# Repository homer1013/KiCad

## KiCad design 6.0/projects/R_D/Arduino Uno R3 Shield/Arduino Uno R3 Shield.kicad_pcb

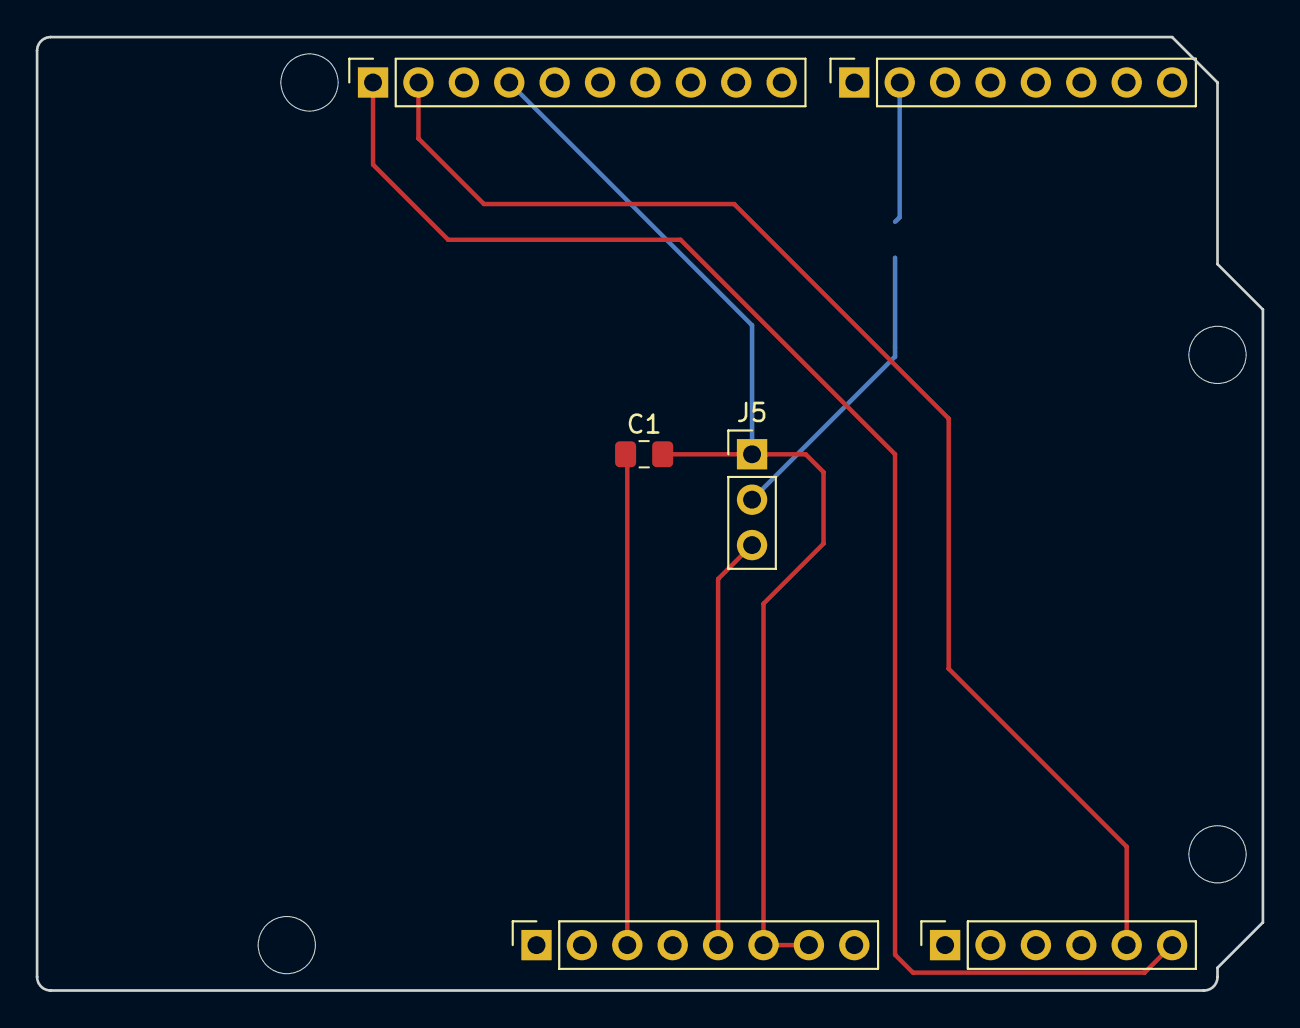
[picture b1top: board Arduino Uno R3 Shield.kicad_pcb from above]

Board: 2 copper layers, 68.6 x 53.3 mm, 11 parts (1 on the bottom side), 7 nets.

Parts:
C1: 10uF; C_0805_2012Metric_Pad1.18x1.45mm_HandSolder
J1: Power; PinSocket_1x08_P2.54mm_Vertical
J2: Digital/PWM; PinSocket_1x10_P2.54mm_Vertical
J3: Analog; PinSocket_1x06_P2.54mm_Vertical
J4: Digital/PWM; PinSocket_1x08_P2.54mm_Vertical
J5: UPDI; PinHeader_1x03_P2.54mm_Vertical
MH1, MH2, MH3, MH4: MountingHole_3.2mm
R1: 4.7ohm; R_0805_2012Metric_Pad1.20x1.40mm_HandSolder

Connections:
+5V: J1.5, J5.3
/*6: J4.2, R1.2
/SCL/A5: J2.1, J3.6
/SDA/A4: J2.2, J3.5
/~RESET: C1.1, J1.3
GND: C1.2, J1.6, J1.7, J2.4, J5.1
unnamed: J5.2, R1.1

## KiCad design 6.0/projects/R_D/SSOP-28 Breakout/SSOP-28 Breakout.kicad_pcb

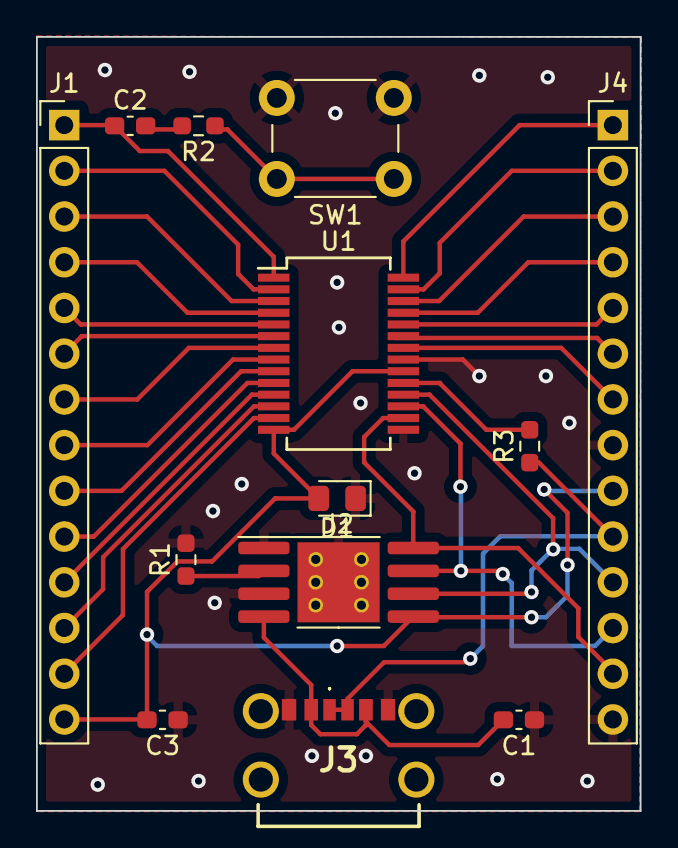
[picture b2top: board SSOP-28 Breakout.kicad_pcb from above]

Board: 2 copper layers, 33.5 x 43.0 mm, 13 parts (0 on the bottom side), 31 nets.

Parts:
C1, C2, C3: 10uF; C_0603_1608Metric_Pad1.08x0.95mm_HandSolder
D1: D_Schottky; D_0805_2012Metric_Pad1.15x1.40mm_HandSolder
J1, J4: Conn_01x14; PinHeader_1x14_P2.54mm_Vertical
J2: TP4056; SOP-8-1EP_4.57x4.57mm_P1.27mm_EP4.57x4.45mm_ThermalVias
J3: USB4125-GF-A-0190; USB4125GFA0190
R1: 2.5K; R_0603_1608Metric_Pad0.98x0.95mm_HandSolder
R2: 1K; R_0603_1608Metric_Pad0.98x0.95mm_HandSolder
R3: 4.7K; R_0603_1608Metric_Pad0.98x0.95mm_HandSolder
SW1: SW_Push_Dual; SW_PUSH_6mm_H5mm
U1: ATMEGA3208-XFR; SSOP-28_5.3x10.2mm_P0.65mm

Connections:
GND: C1.1, C3.1, D1.1 (K), J2.1 (TEMP1), J2.3 (GND_3), J2.9 (EP), J3.A12 (GND_1), J3.B12 (GND_2), J4.8, J4.14, R1.2, SW1.2, U1.15 (GND_1), U1.21 (GND_2)
unnamed: C1.2, J2.4 (VCC4), J3.A9 (VBUS_1), J3.B9 (VBUS_2)
unnamed: C2.1, J1.1, U1.1 (PA7)
unnamed: C2.2, R2.2
unnamed: C3.2, D1.2 (A), J1.14, J2.5 (BAT), J4.9, U1.14 (AVDD), U1.20 (VDD)
unnamed: J1.2, U1.2 (PC0)
unnamed: J1.3, U1.3 (PC1)
unnamed: J1.4, U1.4 (PC2)
unnamed: J1.5, U1.5 (PC3)
unnamed: J1.6, U1.6 (PD0)
unnamed: J1.7, U1.7 (PD1)
unnamed: J1.8, U1.8 (PD2)
unnamed: J1.9, U1.9 (PD3)
unnamed: J1.10, U1.10 (PD4)
unnamed: J1.11, U1.11 (PD5)
unnamed: J1.12, U1.12 (PD6)
unnamed: J1.13, U1.13 (PD7)
unnamed: J2.2 (PROG2), R1.1
unnamed: J2.6 (~STDBY), J4.11, U1.18 (PF6)
unnamed: J2.7 (~CHRG), J4.12, U1.17 (PF1(TOSC2))
unnamed: J2.8 (CE), J4.13, U1.16 (PF0(TOSC1))
unnamed: J3.A5 (CC1), J3.B5 (CC2), J4.10, R3.1
unnamed: J4.1, U1.28 (PA6)
unnamed: J4.2, U1.27 (PA5)
unnamed: J4.3, U1.26 (PA4)
unnamed: J4.4, U1.25 (PA3)
unnamed: J4.5, U1.24 (PA2)
unnamed: J4.6, U1.23 (PA1)
unnamed: J4.7, U1.22 (PA0(EXTCLK))
unnamed: R2.1, SW1.1
unnamed: R3.2, U1.19 (UPDI)

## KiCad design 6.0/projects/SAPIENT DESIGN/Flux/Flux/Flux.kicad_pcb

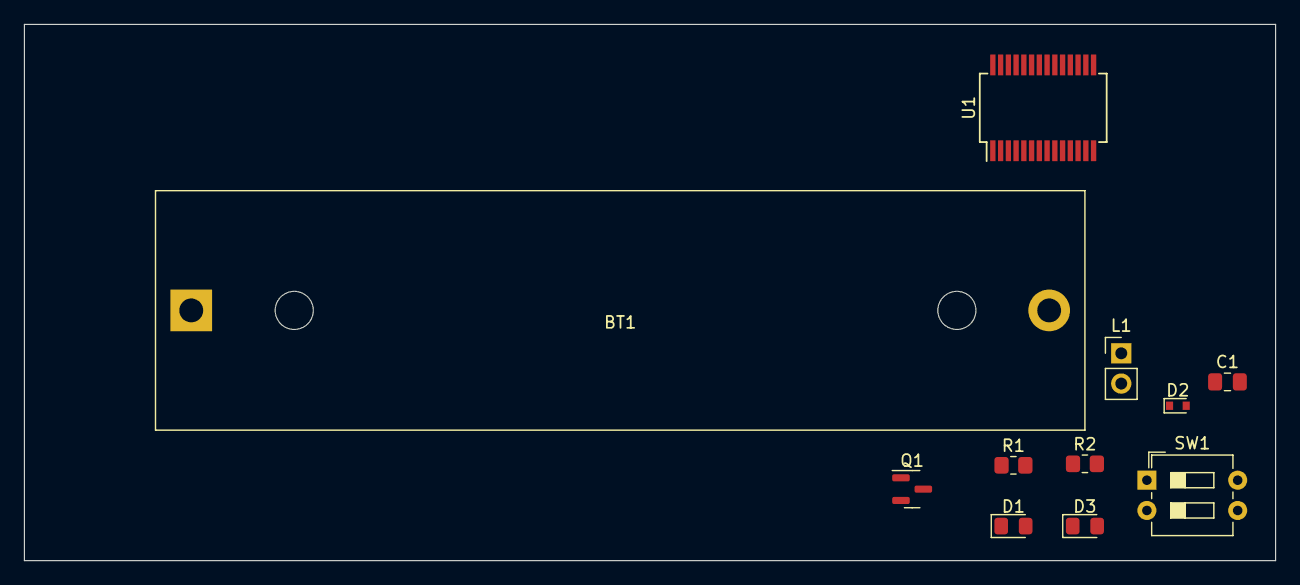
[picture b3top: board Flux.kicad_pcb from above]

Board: 2 copper layers, 105.0 x 45.0 mm, 11 parts (0 on the bottom side), 9 nets, no tracks yet.

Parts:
BT1: Battery_Cell; BatteryHolder_MPD_BH-18650-PC2
C1: C; C_0805_2012Metric_Pad1.18x1.45mm_HandSolder
D1, D3: LED; LED_0805_2012Metric_Pad1.15x1.40mm_HandSolder
D2: 1N914WT; D_SOD-523
L1: L; PinHeader_1x02_P2.54mm_Vertical
Q1: AO3400A; SOT-23
R1, R2: R; R_0805_2012Metric_Pad1.20x1.40mm_HandSolder
SW1: SW_SPDT; SW_DIP_SPSTx02_Slide_6.7x6.64mm_W7.62mm_P2.54mm_LowProfile
U1: ATmega3208-X; SSOP-28_5.3x10.2mm_P0.65mm

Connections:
GND: BT1.2 (-), D1.1 (K), D3.1 (K), Q1.2 (S), U1.15 (GND), U1.21 (GND)
unnamed: BT1.1 (+), C1.1, D2.2 (A)
unnamed: C1.2, L1.2
unnamed: D1.2 (A), R1.1
unnamed: D2.1 (K), SW1.2 (B)
unnamed: D3.2 (A), R2.1
unnamed: L1.1, Q1.3 (D)
unnamed: Q1.1 (G), R1.2, U1.6 (PD0)
unnamed: R2.2, SW1.1 (A), U1.14 (AVDD), U1.20 (VDD)

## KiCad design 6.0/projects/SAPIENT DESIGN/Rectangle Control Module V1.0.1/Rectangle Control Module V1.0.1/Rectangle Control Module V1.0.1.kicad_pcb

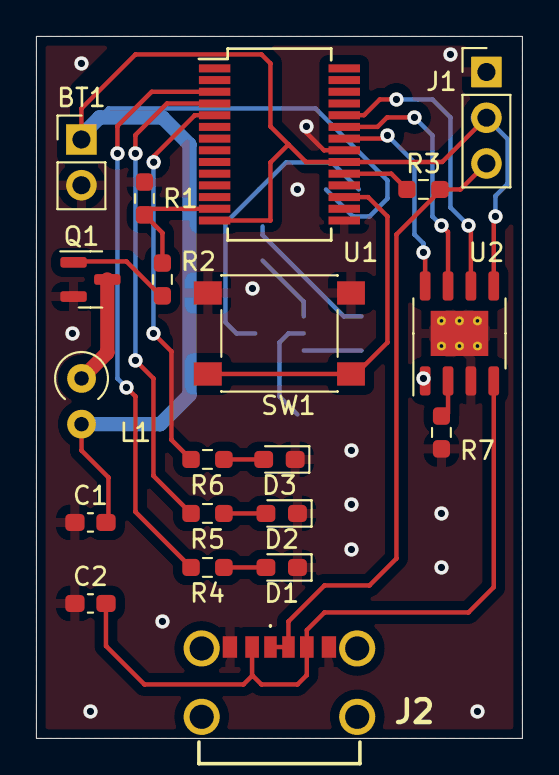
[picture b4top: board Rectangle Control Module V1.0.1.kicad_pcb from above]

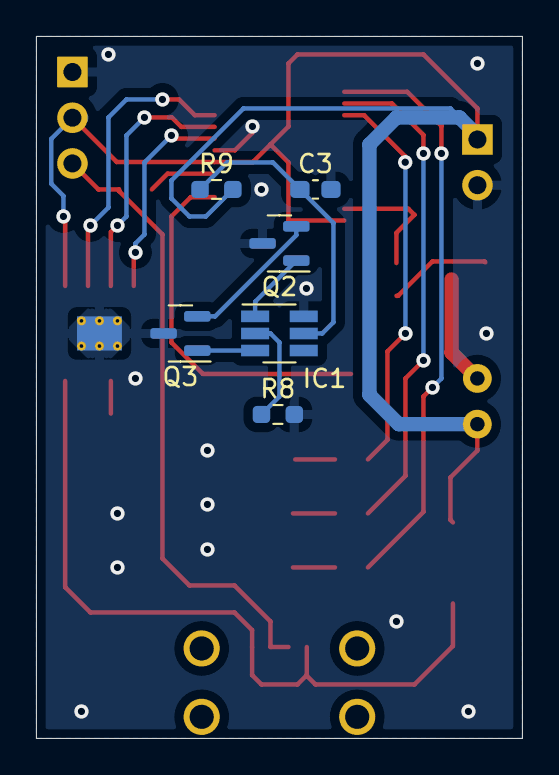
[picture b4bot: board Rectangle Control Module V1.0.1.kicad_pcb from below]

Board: 2 copper layers, 27.0 x 39.0 mm, 26 parts (6 on the bottom side), 24 nets.

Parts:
BT1: Battery_Cell; PinHeader_1x02_P2.54mm_Vertical
C1, C2: 10uF; C_0603_1608Metric_Pad1.08x0.95mm_HandSolder
C3: .1uF; C_0603_1608Metric_Pad1.08x0.95mm_HandSolder
D1, D2, D3: LED; LED_0603_1608Metric_Pad1.05x0.95mm_HandSolder
IC1: DW01A-G; SOT-23-6_Handsoldering
J1: Conn_01x03_Male; PinHeader_1x03_P2.54mm_Vertical
J2: USB4140-GF-0070-C; USB4125GFA0190
L1: 2 Ohm; L_Axial_L6.6mm_D2.7mm_P2.54mm_Vertical_Vishay_IM-2
Q1, Q2, Q3: AO3400A; SOT-23
R1: 100K; R_0603_1608Metric_Pad0.98x0.95mm_HandSolder
R2, R3: 4.7K; R_0603_1608Metric_Pad0.98x0.95mm_HandSolder
R4, R5, R6: 1K; R_0603_1608Metric_Pad0.98x0.95mm_HandSolder
R7: 2.8K; R_0603_1608Metric_Pad0.98x0.95mm_HandSolder
R8: 2K; R_0603_1608Metric_Pad0.98x0.95mm_HandSolder
R9: 330; R_0603_1608Metric_Pad0.98x0.95mm_HandSolder
SW1: btn; SW_Push_1P1T_NO_6x6mm_H9.5mm
U1: ATmega3208-X; SSOP-28_5.3x10.2mm_P0.65mm
U2: TP4056; SOIC-8-1EP_3.9x4.9mm_P1.27mm_EP2.514x3.2mm_ThermalVias

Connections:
GND: BT1.2 (-), C1.1, C2.1, C3.2, D1.1 (K), D2.1 (K), D3.1 (K), IC1.6 (GND), J1.1, J2.A12 (GND_1), J2.B12 (GND_2), Q1.2, Q2.3, Q3.3, R1.1, R7.2, R8.2, SW1.1, U1.15 (GND), U1.21 (GND), U2.1 (TEMP1), U2.3 (GND_3), U2.9 (EP)
unnamed: BT1.1 (+), C1.2, J1.2, L1.2, R9.2, U1.14 (AVDD), U1.20 (VDD), U2.5 (BAT)
unnamed: C2.2, J2.A9 (VBUS_1), J2.B9 (VBUS_2), U2.4 (VCC4)
unnamed: C3.1, IC1.5 (VCC), R9.1
unnamed: D1.2 (A), R4.1
unnamed: D2.2 (A), R5.1
unnamed: D3.2 (A), R6.1
unnamed: IC1.1 (OD), Q2.1
unnamed: IC1.2 (CS), R8.1
unnamed: IC1.3 (OC), Q3.1
unnamed: J1.3, J2.A5 (CC1), J2.B5 (CC2), R3.2
unnamed: L1.1, Q1.3
unnamed: Q1.1, R2.1
unnamed: Q2.2, Q3.2
unnamed: R1.2, R2.2, U1.13 (PD7)
unnamed: R3.1, U1.19 (UPDI)
unnamed: R4.2, U1.3 (PC1)
unnamed: R5.2, U1.4 (PC2)
unnamed: R6.2, U1.5 (PC3)
unnamed: R7.1, U2.2 (PROG2)
unnamed: SW1.2, U1.17 (PF1/TOSC2)
unnamed: U1.22 (EXTCLK/PA0), U2.8 (CE)
unnamed: U1.23 (PA1), U2.7 (~CHRG)
unnamed: U1.24 (PA2), U2.6 (~STDBY)

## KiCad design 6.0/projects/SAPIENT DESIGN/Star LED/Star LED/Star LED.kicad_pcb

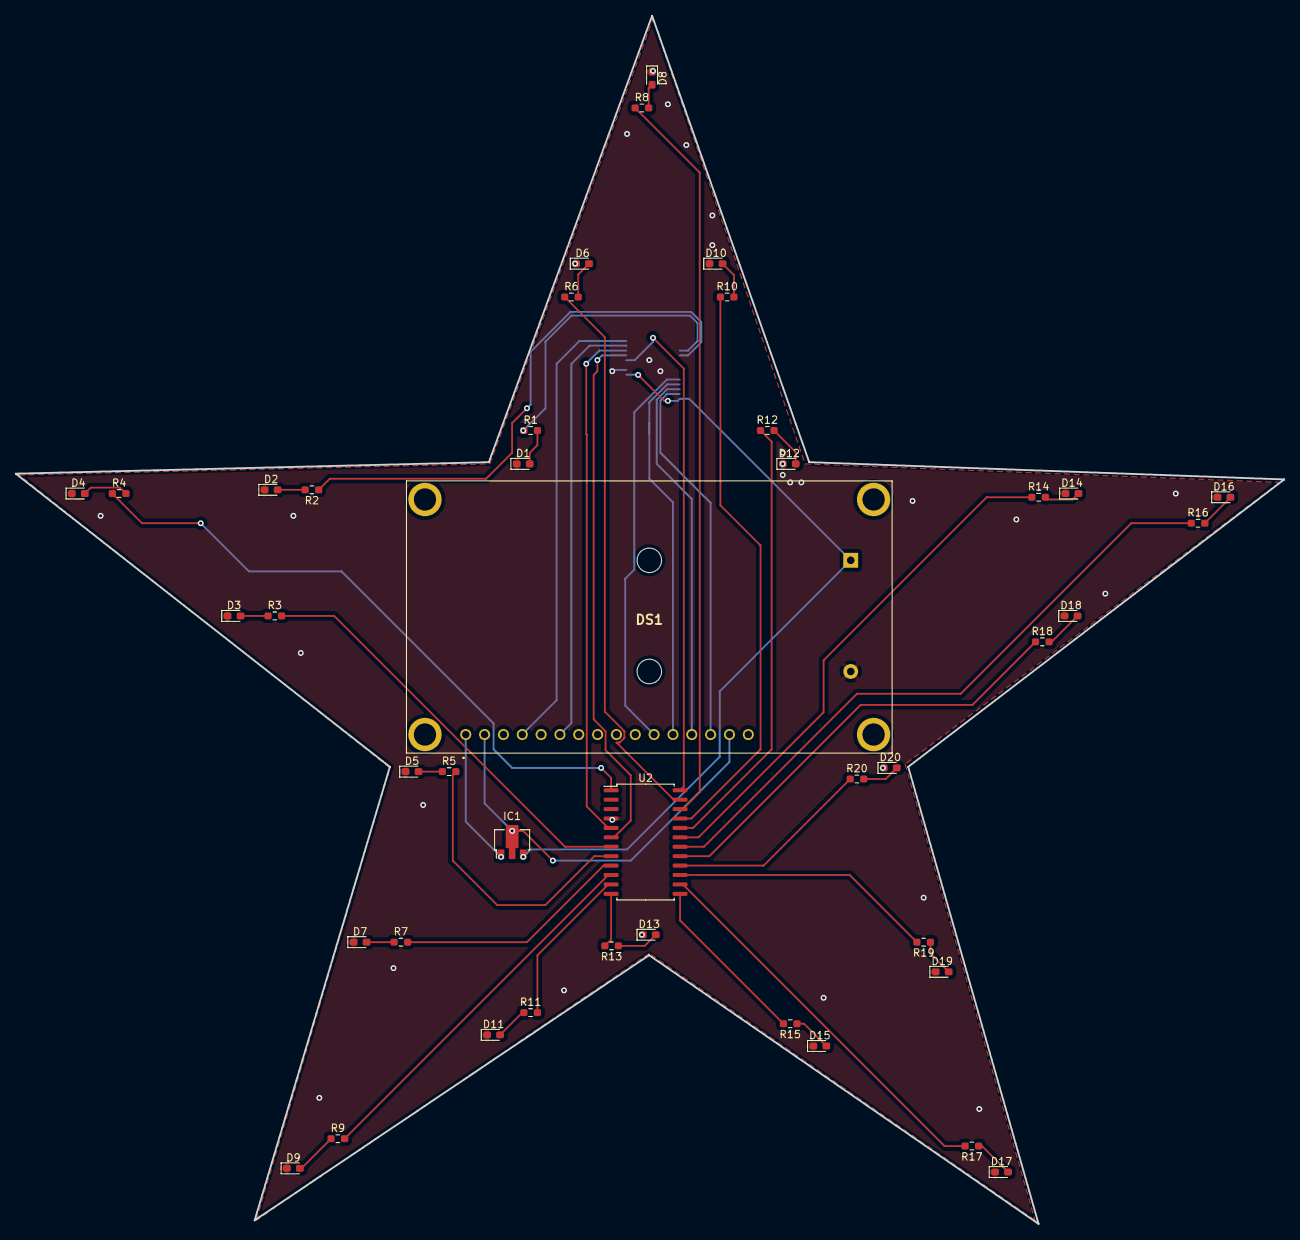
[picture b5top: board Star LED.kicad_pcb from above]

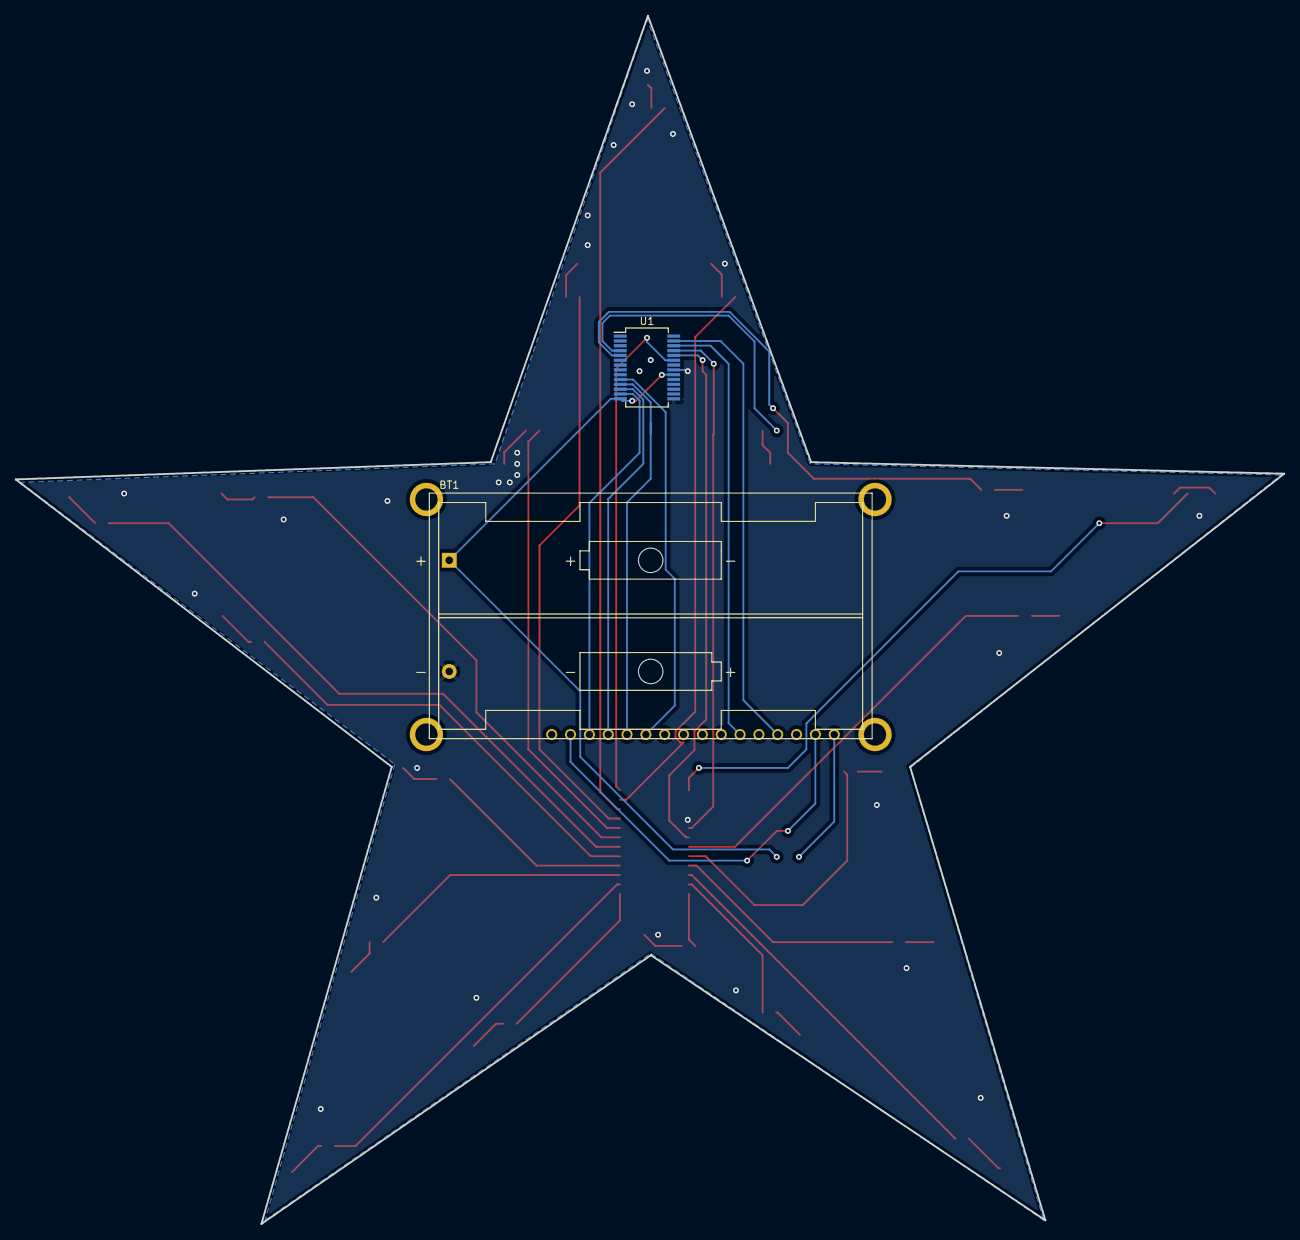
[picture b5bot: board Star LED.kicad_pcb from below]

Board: 2 copper layers, 171.1 x 162.9 mm, 45 parts (2 on the bottom side), 53 nets.

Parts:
BT1: Battery; BatteryHolder_Keystone_2462_2xAA
D1, D2, D3, D4, D5, D6, D7, D8, D9, D10, D11, D12, D13, D14, D15, D16, D17, D18, D19, D20: LED; LED_0603_1608Metric_Pad1.05x0.95mm_HandSolder
DS1: NHD-0216HZ-FSW-FBW-33V3C; NHD0216HZFSWFBW33V3C
IC1: MCP1702T-3302E_CB; SOT-89-3
R1, R2, R3, R4, R5, R6, R7, R8, R9, R10, R11, R12, R13, R14, R15, R16, R17, R18, R19, R20: R; R_0603_1608Metric_Pad0.98x0.95mm_HandSolder
U1: ATmega3208-X; SSOP-28_5.3x10.2mm_P0.65mm
U2: IS31FL3218-GR; SOP-24_7.5x15.4mm_P1.27mm

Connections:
GND: BT1.2 (-), D1.1 (K), D2.1 (K), D3.1 (K), D4.1 (K), D5.1 (K), D6.1 (K), D7.1 (K), D8.1 (K), D9.1 (K), D10.1 (K), D11.1 (K), D12.1 (K), D13.1 (K), D14.1 (K), D15.1 (K), D16.1 (K), D17.1 (K), D18.1 (K), D19.1 (K), D20.1 (K), U1.15 (GND), U1.21 (GND), U2.4 (GND)
unnamed: BT1.1 (+), IC1.3 (VIN), U1.14 (AVDD), U1.20 (VDD)
unnamed: D1.2 (A), R1.2
unnamed: D2.2 (A), R2.2
unnamed: D3.2 (A), R3.1
unnamed: D4.2 (A), R4.2
unnamed: D5.2 (A), R5.1
unnamed: D6.2 (A), R6.2
unnamed: D7.2 (A), R7.1
unnamed: D8.2 (A), R8.2
unnamed: D9.2 (A), R9.1
unnamed: D10.2 (A), R10.2
unnamed: D11.2 (A), R11.1
unnamed: D12.2 (A), R12.2
unnamed: D13.2 (A), R13.1
unnamed: D14.2 (A), R14.2
unnamed: D15.2 (A), R15.1
unnamed: D16.2 (A), R16.2
unnamed: D17.2 (A), R17.1
unnamed: D18.2 (A), R18.2
unnamed: D19.2 (A), R19.1
unnamed: D20.2 (A), R20.2
unnamed: DS1.1 (VSS), DS1.5 (R/W), DS1.16 (LED-), IC1.1 (GND)
unnamed: DS1.4 (RS), U1.27 (PA5)
unnamed: DS1.6 (E), U1.26 (PA4)
unnamed: DS1.11 (DB4), U1.10 (PD4)
unnamed: DS1.12 (DB5), U1.11 (PD5)
unnamed: DS1.13 (DB6), U1.12 (PD6)
unnamed: DS1.14 (DB7), U1.13 (PD7)
unnamed: DS1.2 (VDD), DS1.15 (LED+), IC1.2 (VOUT)
unnamed: R1.1, U1.4 (PC2)
unnamed: R2.1, U1.5 (PC3)
unnamed: R3.2, U2.7 (OUT1)
unnamed: R4.1, U2.1 (OUT18)
unnamed: R5.2, U2.8 (OUT2)
unnamed: R6.1, U2.23 (OUT17)
unnamed: R7.2, U2.9 (OUT3)
unnamed: R8.1, U2.22 (OUT16)
unnamed: R9.2, U2.10 (OUT4)
unnamed: R10.1, U2.21 (OUT15)
unnamed: R11.2, U2.11 (OUT5)
unnamed: R12.1, U2.20 (OUT14)
unnamed: R13.2, U2.12 (OUT6)
unnamed: R14.1, U2.19 (OUT13)
unnamed: R15.2, U2.13 (OUT7)
unnamed: R16.1, U2.18 (OUT12)
unnamed: R17.2, U2.14 (OUT8)
unnamed: R18.1, U2.17 (OUT11)
unnamed: R19.2, U2.15 (OUT9)
unnamed: R20.1, U2.16 (OUT10)
unnamed: U1.23 (PA1), U2.24 (~SDB)
unnamed: U1.24 (PA2), U2.6 (SCL)
unnamed: U1.25 (PA3), U2.5 (SDA)

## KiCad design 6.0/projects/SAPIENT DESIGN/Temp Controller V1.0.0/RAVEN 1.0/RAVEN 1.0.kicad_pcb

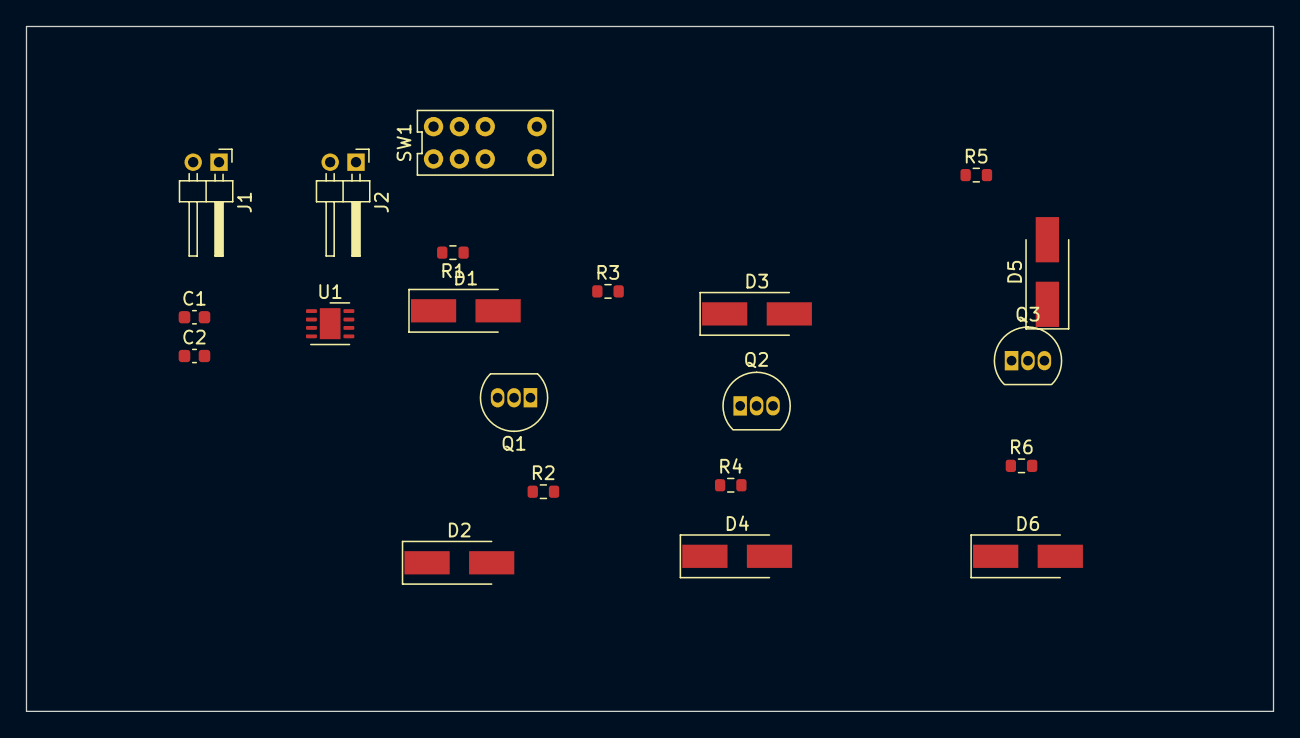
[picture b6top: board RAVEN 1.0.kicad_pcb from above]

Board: 2 copper layers, 96.5 x 53.0 mm, 21 parts (0 on the bottom side), 14 nets, no tracks yet.

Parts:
C1, C2: 1uf; C_0603_1608Metric
D1, D2, D3, D4, D5, D6: D_Schottky; D_SMA_Handsoldering
J1, J2: Conn_01x02_Female; PinHeader_1x02_P2.00mm_Horizontal
Q1, Q2, Q3: 2N3905; TO-92_Inline
R1: 39.2K; R_0603_1608Metric
R2: 36.5K; R_0603_1608Metric
R3: 46.4K; R_0603_1608Metric
R4: 30.9K; R_0603_1608Metric
R5: 52K; R_0603_1608Metric
R6: 28K; R_0603_1608Metric
SW1: OS203011MS1QP1
U1: TPS73701DRBR; HVSON-8-1EP_3x3mm_P0.65mm_EP1.6x2.4mm

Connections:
GND: C1.1, C2.1, D2.1 (K), D4.1 (K), D6.1 (K), J1.2, J2.2, U1.4 (GND), U1.9 (EPAD)
unnamed: C2.2, J2.1, U1.5 (EN), U1.8 (IN)
unnamed: C1.2, J1.1, Q1.2 (B), Q2.2 (B), R1.1, R3.1, SW1.1 (NO_1), SW1.2 (NO_2), SW1.3 (C_1), U1.1 (OUT)
unnamed: D1.2 (A), R1.2
unnamed: Q1.1 (E), R2.1
unnamed: D2.2 (A), R2.2
unnamed: D3.2 (A), R3.2
unnamed: Q2.1 (E), R4.1
unnamed: D4.2 (A), R4.2
unnamed: Q3.2 (B), R5.1, SW1.4 (NC_1)
unnamed: D5.2 (A), R5.2
unnamed: Q3.1 (E), R6.1
unnamed: D6.2 (A), R6.2
unnamed: D1.1 (K), D3.1 (K), D5.1 (K), Q1.3 (C), Q2.3 (C), Q3.3 (C), U1.3 (FB)
